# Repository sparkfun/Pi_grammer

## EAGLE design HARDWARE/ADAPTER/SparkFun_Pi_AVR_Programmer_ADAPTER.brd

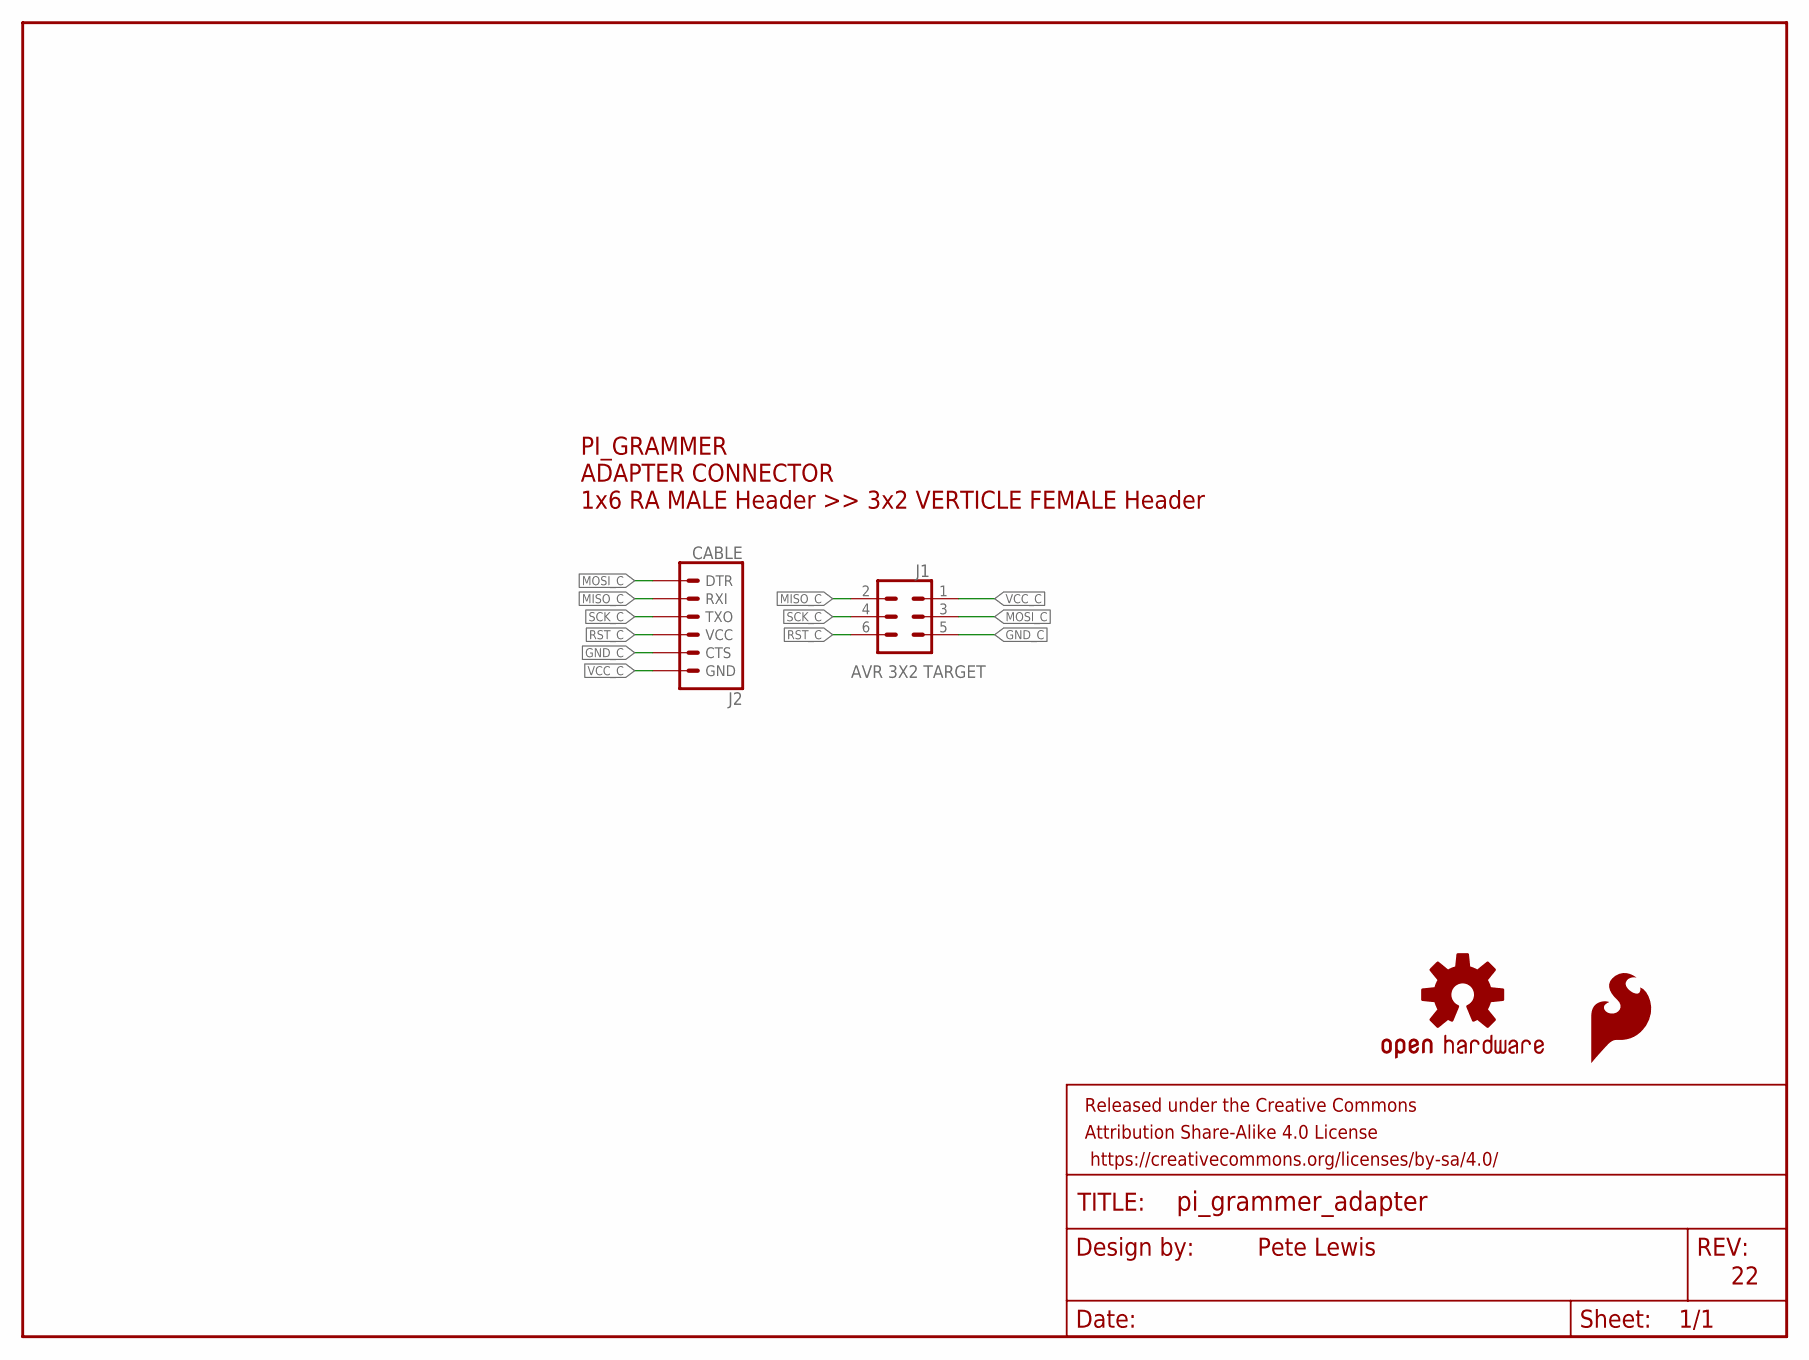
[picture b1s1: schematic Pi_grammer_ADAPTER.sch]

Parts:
FRAME1: FRAME-LETTER; CREATIVE_COMMONS
J1: AVR 3X2 TARGET; 2X3_SMT_POSTS
J2: CABLE; 1X06-SMD_RA_MALE
LOGO1: SFE_LOGO_FLAME.1_INCH; SFE_LOGO_FLAME_.1
LOGO2: OSHW-LOGOMINI; OSHW-LOGO-MINI

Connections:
GND_C: J1.5, J2.5 (CTS)
MISO_C: J1.2, J2.2 (RXI)
MOSI_C: J1.3, J2.1 (DTR)
RST_C: J1.6, J2.4 (VCC)
SCK_C: J1.4, J2.3 (TXO)
VCC_C: J1.1, J2.6 (GND)

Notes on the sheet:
PI_GRAMMER ADAPTER CONNECTOR 1x6 RA MALE Header >> 3x2 VERTICLE FEMALE Header
Pete Lewis

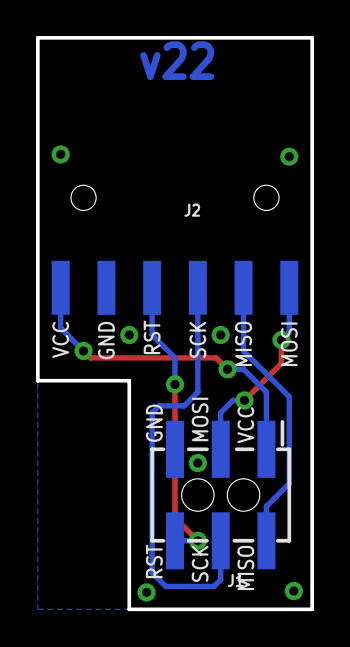
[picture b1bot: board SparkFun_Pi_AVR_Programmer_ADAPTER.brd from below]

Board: 2 copper layers, 15.2 x 31.8 mm, 16 parts (2 on the bottom side), 6 nets.

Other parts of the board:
U$1: GND1
U$2: MISO5
U$3: MOSI4
U$4: RST2
U$5: SCK3
U$6: VCC0
U$7: PI0
U$8: AVR1
U$9: PROGRAMMER2
U$10: HAT3
U$11: ADAPTER4

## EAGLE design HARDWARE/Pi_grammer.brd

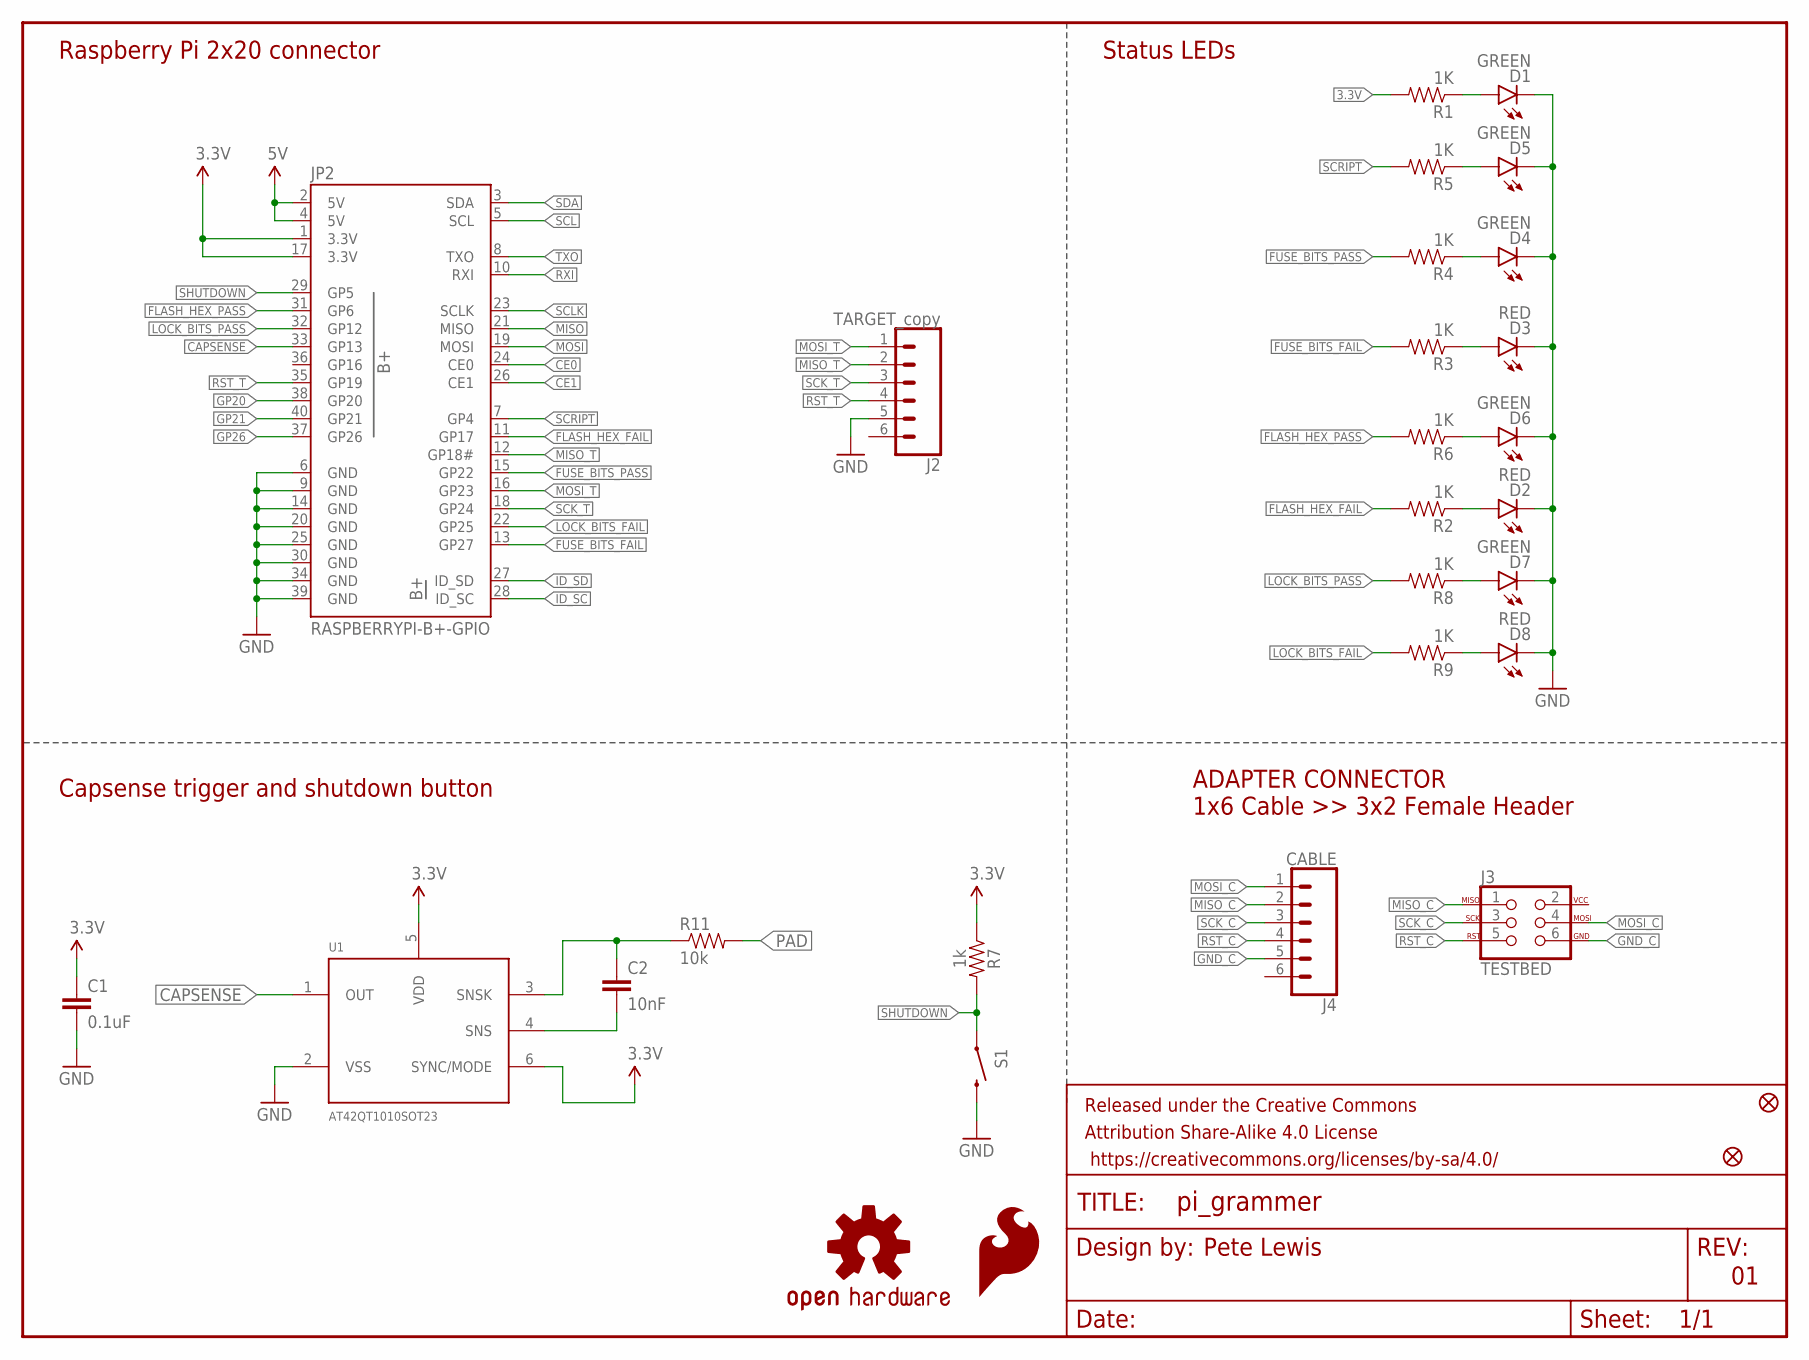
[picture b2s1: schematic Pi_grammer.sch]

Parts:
C1: 0.1uF; 0603-CAP
C2: 10nF; 0603-CAP
D1, D4, D5, D6, D7: GREEN; LED-1206
D2, D3, D8: RED; LED-1206
FD1, FD2: FIDUCIALUFIDUCIAL; FIDUCIAL-MICRO
FRAME1: FRAME-LETTER; CREATIVE_COMMONS
J2: TARGET_copy; MOLEX-1X6
J3: TESTBED; 2X3_LOCK
J4: CABLE; MOLEX-1X6-RA
JP2: RASPBERRYPI-B+-GPIO; 2X20-SHROUDED
LOGO1: SFE_LOGO_FLAME.1_INCH; SFE_LOGO_FLAME_.1
LOGO2: OSHW-LOGOS; OSHW-LOGO-S
R1, R2, R3, R4, R5, R6, R8, R9: 1K; 0603-RES
R7: 1k; 0603
R11: 10k; 0603-RES
S1: SWITCH-MOMENTARY-2SMD; TACTILE-SWITCH-SMD
U1: AT42QT1010SOT23; SOT23-6

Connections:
3.3V: C1.1, JP2.1 (3.3V), JP2.17 (3.3V), R1.2, R7.1, U1.5 (VDD), U1.6 (SYNC/MODE)
5V: JP2.2 (5V), JP2.4 (5V)
CAPSENSE: JP2.33 (GP13), U1.1 (OUT)
CE0: JP2.24 (CE0)
CE1: JP2.26 (CE1)
FLASH_HEX_FAIL: JP2.11 (GP17), R2.2
FLASH_HEX_PASS: JP2.31 (GP6), R6.2
FUSE_BITS_FAIL: JP2.13 (GP27), R3.2
FUSE_BITS_PASS: JP2.15 (GP22), R4.2
GND: C1.2, D1.C, D2.C, D3.C, D4.C, D5.C, D6.C, D7.C, D8.C, J2.5, JP2.6 (GND), JP2.9 (GND), JP2.14 (GND), JP2.20 (GND), JP2.25 (GND), JP2.30 (GND), JP2.34 (GND), JP2.39 (GND), S1.3 (2), U1.2 (VSS)
GND_C: J3.6, J4.5
GP20: JP2.38 (GP20)
GP21: JP2.40 (GP21)
GP26: JP2.37 (GP26)
ID_SC: JP2.28 (ID_SC)
ID_SD: JP2.27 (ID_SD)
LOCK_BITS_FAIL: JP2.22 (GP25), R9.2
LOCK_BITS_PASS: JP2.32 (GP12), R8.2
MISO: JP2.21 (MISO)
MISO_C: J3.1, J4.2
MISO_T: J2.2, JP2.12 (GP18#)
MOSI: JP2.19 (MOSI)
MOSI_C: J3.4, J4.1
MOSI_T: J2.1, JP2.16 (GP23)
unnamed: D6.A, R6.1
unnamed: D1.A, R1.1
unnamed: D2.A, R2.1
unnamed: D3.A, R3.1
unnamed: D7.A, R8.1
unnamed: D4.A, R4.1
unnamed: D5.A, R5.1
unnamed: D8.A, R9.1
unnamed: C2.2, U1.4 (SNS)
unnamed: C2.1, R11.1, U1.3 (SNSK)
PAD: R11.2
RST_C: J3.5, J4.4
RST_T: J2.4, JP2.35 (GP19)
RXI: JP2.10 (RXI)
SCK_C: J3.3, J4.3
SCK_T: J2.3, JP2.18 (GP24)
SCL: JP2.5 (SCL)
SCLK: JP2.23 (SCLK)
SCRIPT: JP2.7 (GP4), R5.2
SDA: JP2.3 (SDA)
SHUTDOWN: JP2.29 (GP5), R7.2, S1.1
TXO: JP2.8 (TXO)

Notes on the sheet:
ADAPTER CONNECTOR 1x6 Cable >> 3x2 Female Header
Raspberry Pi 2x20 connector
Pete Lewis
Status LEDs
Capsense trigger and shutdown button

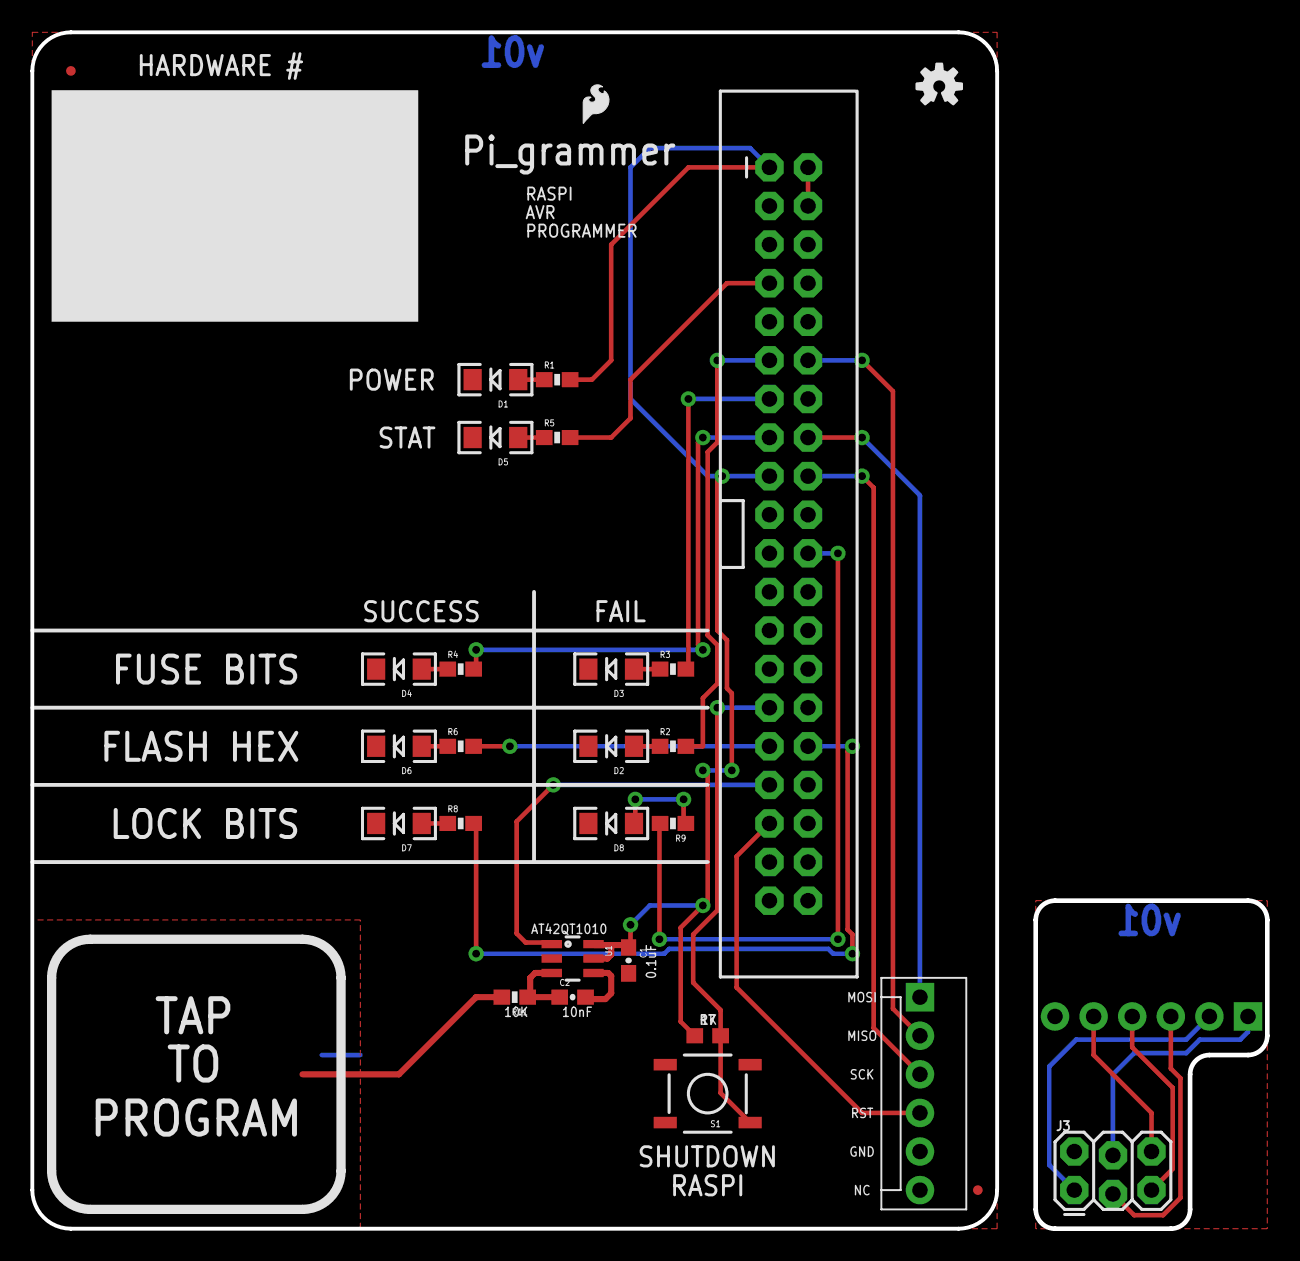
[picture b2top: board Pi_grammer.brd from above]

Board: 2 copper layers, 63.5 x 78.7 mm, 31 parts (1 on the bottom side), 31 nets.

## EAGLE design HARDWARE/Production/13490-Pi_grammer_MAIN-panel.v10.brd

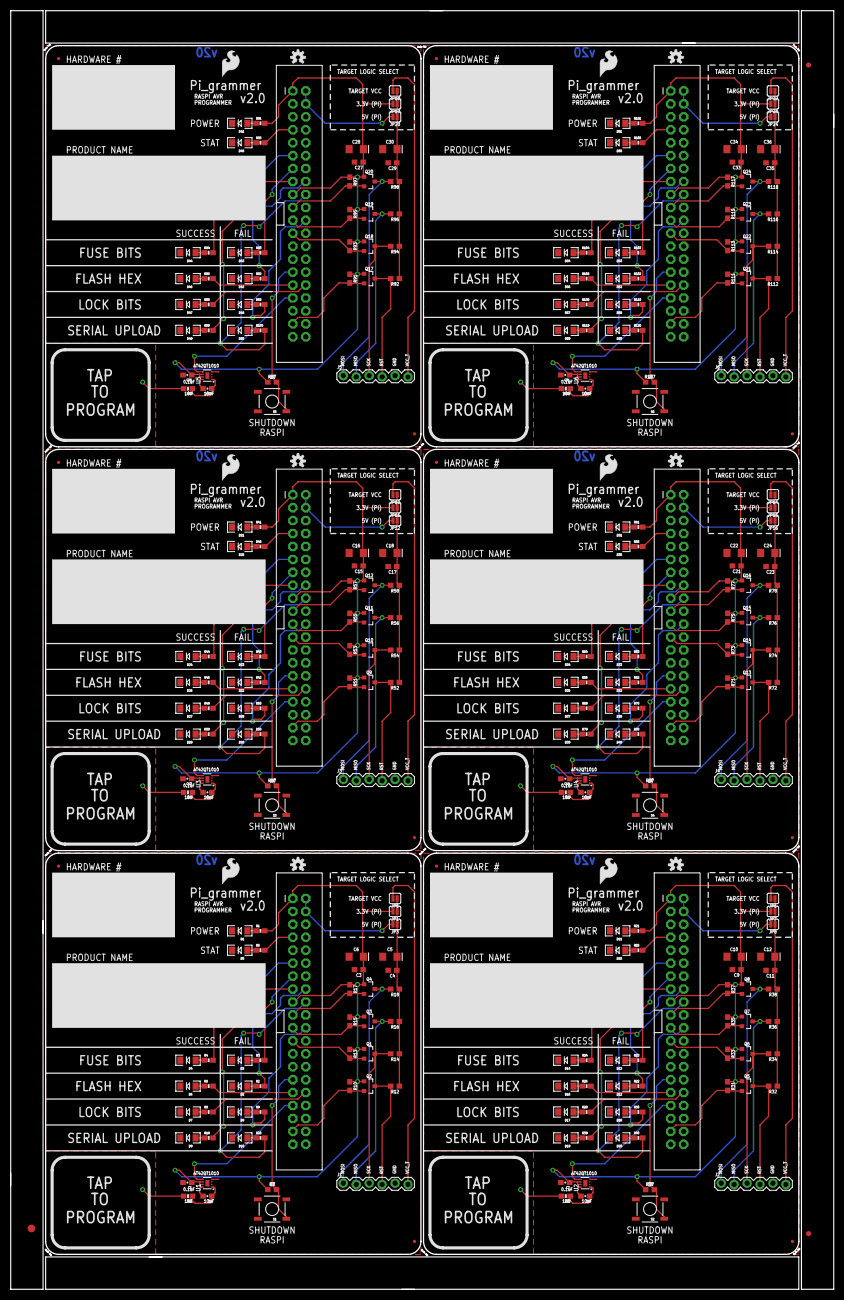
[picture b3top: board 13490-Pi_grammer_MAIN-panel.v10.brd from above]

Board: 2 copper layers, 161.5 x 251.0 mm, 309 parts (0 on the bottom side), 216 nets.

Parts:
C1, C7, C13, C19, C25, C31: 0.1uF; 0603-CAP
C2, C8, C14, C20, C26, C32: 10nF; 0603-CAP
C3, C4, C9, C11, C15, C17, C21, C23, C27, C29, C33, C35: 0.1uF; 0603
C5, C6, C10, C12, C16, C18, C22, C24, C28, C30, C34, C36: 10uF; EIA3216
D1, D4, D5, D6, D7, D9, D11, D14, D15, D16, D17, D19, D21, D24, D25, D26, D27, D29, D31, D34, D35, D36, D37, D39, D41, D44, D45, D46, D47, D49, D51, D54, D55, D56, D57, D59: GREEN; LED-1206
D2, D3, D8, D10, D12, D13, D18, D20, D22, D23, D28, D30, D32, D33, D38, D40, D42, D43, D48, D50, D52, D53, D58, D60: RED; LED-1206
E$1: FIDUCIAL-1.5X3
E$7, E$8: FIDUCIAL-1X2
FD1, FD2, FD3, FD4, FD5, FD6, FD7, FD8, FD9, FD10, FD11, FD12: FIDUCIALUFIDUCIAL; MICRO-FIDUCIAL
J1, J2, J3, J4, J5, J6: TARGET_copy; 1X06_LOCK
JP1, JP3, JP5, JP6, JP7, JP8, JP10, JP11, JP12, JP14, JP15, JP16, JP18, JP19, JP20, JP22, JP23, JP24: SMT-JUMPER_2_NO_SILK
JP2, JP4, JP9, JP13, JP17, JP21: RASPBERRYPI-B+-GPIO; 2X20-SHROUDED
LOGO1, LOGO4, LOGO6, LOGO8, LOGO10, LOGO12: SFE_LOGO_FLAME.2_INCH; SFE_LOGO_FLAME_.2
LOGO2, LOGO3, LOGO5, LOGO7, LOGO9, LOGO11: OSHW-LOGOS; OSHW-LOGO-S
Q1, Q2, Q3, Q4, Q5, Q6, Q7, Q8, Q9, Q10, Q11, Q12, Q13, Q14, Q15, Q16, Q17, Q18, Q19, Q20, Q21, Q22, Q23, Q24: 220mA/50V/3.5Ω; SOT23-3
R1, R2, R3, R4, R5, R6, R8, R9, R19, R20, R21, R22, R23, R24, R25, R26, R28, R30, R39, R40, R41, R42, R43, R44, R45, R46, R48, R50, R59, R60, R61, R62, R63, R64, R65, R66, R68, R70, R79, R80, R81, R82, R83, R84, R85, R86, R88, R90, R99, R100, R101, R102, R103, R104, R105, R106, R108, R110, R119, R120: 1K; 0603-RES
R7, R27, R47, R67, R87, R107: 1k; 0603
R10, R12, R13, R14, R15, R16, R17, R18, R31, R32, R33, R34, R35, R36, R37, R38, R51, R52, R53, R54, R55, R56, R57, R58, R71, R72, R73, R74, R75, R76, R77, R78, R91, R92, R93, R94, R95, R96, R97, R98, R111, R112, R113, R114, R115, R116, R117, R118: 10k; 0603
R11, R29, R49, R69, R89, R109: 10k; 0603-RES
S1, S2, S3, S4, S5, S6: TACTILE-SWITCH-SMD
U1, U2, U3, U4, U5, U6: AT42QT1010UDFN; UDFN/USON_8_PAD

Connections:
3.3V: C1.1, C3.1, C6.+, JP1.2, JP2.1, JP2.17, Q1.1, Q2.1, Q3.1, Q4.1, R1.2, R7.1, R10.1, R13.1, R15.1, R17.1, U1.6, U1.7
3.3V1: C7.1, C9.1, C10.+, JP4.1, JP4.17, JP7.2, Q5.1, Q6.1, Q7.1, Q8.1, R21.2, R27.1, R31.1, R33.1, R35.1, R37.1, U2.6, U2.7
3.3V2: C13.1, C15.1, C16.+, JP9.1, JP9.17, JP11.2, Q9.1, Q10.1, Q11.1, Q12.1, R41.2, R47.1, R51.1, R53.1, R55.1, R57.1, U3.6, U3.7
3.3V3: C19.1, C21.1, C22.+, JP13.1, JP13.17, JP15.2, Q13.1, Q14.1, Q15.1, Q16.1, R61.2, R67.1, R71.1, R73.1, R75.1, R77.1, U4.6, U4.7
3.3V4: C25.1, C27.1, C28.+, JP17.1, JP17.17, JP19.2, Q17.1, Q18.1, Q19.1, Q20.1, R81.2, R87.1, R91.1, R93.1, R95.1, R97.1, U5.6, U5.7
3.3V5: C31.1, C33.1, C34.+, JP21.1, JP21.17, JP23.2, Q21.1, Q22.1, Q23.1, Q24.1, R101.2, R107.1, R111.1, R113.1, R115.1, R117.1, U6.6, U6.7
5V: JP2.2, JP2.4, JP3.2
5V1: JP4.2, JP4.4, JP8.2
5V2: JP9.2, JP9.4, JP12.2
5V3: JP13.2, JP13.4, JP16.2
5V4: JP17.2, JP17.4, JP20.2
5V5: JP21.2, JP21.4, JP24.2
CAPSENSE: JP2.33, U1.5
CAPSENSE1: JP4.33, U2.5
CAPSENSE2: JP9.33, U3.5
CAPSENSE3: JP13.33, U4.5
CAPSENSE4: JP17.33, U5.5
CAPSENSE5: JP21.33, U6.5
FLASH_HEX_FAIL: JP2.11, R2.2
FLASH_HEX_FAIL1: JP4.11, R22.2
FLASH_HEX_FAIL2: JP9.11, R42.2
FLASH_HEX_FAIL3: JP13.11, R62.2
FLASH_HEX_FAIL4: JP17.11, R82.2
FLASH_HEX_FAIL5: JP21.11, R102.2
FLASH_HEX_PASS: JP2.31, R6.2
FLASH_HEX_PASS1: JP4.31, R26.2
FLASH_HEX_PASS2: JP9.31, R46.2
FLASH_HEX_PASS3: JP13.31, R66.2
FLASH_HEX_PASS4: JP17.31, R86.2
FLASH_HEX_PASS5: JP21.31, R106.2
FUSE_BITS_FAIL: JP2.13, R3.2
FUSE_BITS_FAIL1: JP4.13, R23.2
FUSE_BITS_FAIL2: JP9.13, R43.2
FUSE_BITS_FAIL3: JP13.13, R63.2
FUSE_BITS_FAIL4: JP17.13, R83.2
FUSE_BITS_FAIL5: JP21.13, R103.2
FUSE_BITS_PASS: JP2.15, R4.2
FUSE_BITS_PASS1: JP4.15, R24.2
FUSE_BITS_PASS2: JP9.15, R44.2
FUSE_BITS_PASS3: JP13.15, R64.2
FUSE_BITS_PASS4: JP17.15, R84.2
FUSE_BITS_PASS5: JP21.15, R104.2
GND: C1.2, C3.2, C4.2, C5.-, C6.-, D1.C, D2.C, D3.C, D4.C, D5.C, D6.C, D7.C, D8.C, D9.C, D10.C, J1.5, JP2.6, JP2.9, JP2.14, JP2.20, JP2.25, JP2.30, JP2.34, JP2.39, S1.3, U1.4
GND1: C7.2, C9.2, C10.-, C11.2, C12.-, D11.C, D12.C, D13.C, D14.C, D15.C, D16.C, D17.C, D18.C, D19.C, D20.C, J2.5, JP4.6, JP4.9, JP4.14, JP4.20, JP4.25, JP4.30, JP4.34, JP4.39, S2.3, U2.4
GND2: C13.2, C15.2, C16.-, C17.2, C18.-, D21.C, D22.C, D23.C, D24.C, D25.C, D26.C, D27.C, D28.C, D29.C, D30.C, J3.5, JP9.6, JP9.9, JP9.14, JP9.20, JP9.25, JP9.30, JP9.34, JP9.39, S3.3, U3.4
GND3: C19.2, C21.2, C22.-, C23.2, C24.-, D31.C, D32.C, D33.C, D34.C, D35.C, D36.C, D37.C, D38.C, D39.C, D40.C, J4.5, JP13.6, JP13.9, JP13.14, JP13.20, JP13.25, JP13.30, JP13.34, JP13.39, S4.3, U4.4
GND4: C25.2, C27.2, C28.-, C29.2, C30.-, D41.C, D42.C, D43.C, D44.C, D45.C, D46.C, D47.C, D48.C, D49.C, D50.C, J5.5, JP17.6, JP17.9, JP17.14, JP17.20, JP17.25, JP17.30, JP17.34, JP17.39, S5.3, U5.4
GND5: C31.2, C33.2, C34.-, C35.2, C36.-, D51.C, D52.C, D53.C, D54.C, D55.C, D56.C, D57.C, D58.C, D59.C, D60.C, J6.5, JP21.6, JP21.9, JP21.14, JP21.20, JP21.25, JP21.30, JP21.34, JP21.39, S6.3, U6.4
LOCK_BITS_FAIL: JP2.22, R9.2
LOCK_BITS_FAIL1: JP4.22, R30.2
LOCK_BITS_FAIL2: JP9.22, R50.2
LOCK_BITS_FAIL3: JP13.22, R70.2
LOCK_BITS_FAIL4: JP17.22, R90.2
LOCK_BITS_FAIL5: JP21.22, R110.2
LOCK_BITS_PASS: JP2.32, R8.2
LOCK_BITS_PASS1: JP4.32, R28.2
LOCK_BITS_PASS2: JP9.32, R48.2
LOCK_BITS_PASS3: JP13.32, R68.2
LOCK_BITS_PASS4: JP17.32, R88.2
LOCK_BITS_PASS5: JP21.32, R108.2
MISO: JP2.21, Q3.2, R15.2
MISO1: JP4.21, Q7.2, R35.2
MISO2: JP9.21, Q11.2, R55.2
MISO3: JP13.21, Q15.2, R75.2
MISO4: JP17.21, Q19.2, R95.2
MISO5: JP21.21, Q23.2, R115.2
MISO_T: J1.2, Q3.3, R16.2
MISO_T1: J2.2, Q7.3, R36.2
MISO_T2: J3.2, Q11.3, R56.2
MISO_T3: J4.2, Q15.3, R76.2
MISO_T4: J5.2, Q19.3, R96.2
MISO_T5: J6.2, Q23.3, R116.2
MOSI: JP2.19, Q4.2, R17.2
MOSI1: JP4.19, Q8.2, R37.2
MOSI2: JP9.19, Q12.2, R57.2
MOSI3: JP13.19, Q16.2, R77.2
MOSI4: JP17.19, Q20.2, R97.2
MOSI5: JP21.19, Q24.2, R117.2
MOSI_T: J1.1, Q4.3, R18.2
MOSI_T1: J2.1, Q8.3, R38.2
MOSI_T2: J3.1, Q12.3, R58.2
MOSI_T3: J4.1, Q16.3, R78.2
MOSI_T4: J5.1, Q20.3, R98.2
MOSI_T5: J6.1, Q24.3, R118.2
unnamed: D6.A, R6.1
unnamed: D1.A, R1.1
unnamed: D2.A, R2.1
unnamed: D3.A, R3.1
unnamed: D7.A, R8.1
unnamed: D4.A, R4.1
unnamed: D5.A, R5.1
unnamed: D8.A, R9.1
unnamed: C4.1, C5.+, JP1.1, JP3.1, JP5.1, R12.1, R14.1, R16.1, R18.1
unnamed: C2.2, U1.8
unnamed: C2.1, R11.1, U1.1
unnamed: D11.A, R21.1
unnamed: D9.A, R19.1
unnamed: D10.A, R20.1
unnamed: D12.A, R22.1
unnamed: D13.A, R23.1
unnamed: D14.A, R24.1
unnamed: D15.A, R25.1
unnamed: D16.A, R26.1
unnamed: D17.A, R28.1
unnamed: C8.2, U2.8
unnamed: C8.1, R29.1, U2.1
unnamed: D18.A, R30.1
unnamed: D19.A, R39.1
unnamed: D20.A, R40.1
unnamed: C11.1, C12.+, JP6.1, JP7.1, JP8.1, R32.1, R34.1, R36.1, R38.1
unnamed: D21.A, R41.1
unnamed: D22.A, R42.1
unnamed: D23.A, R43.1
unnamed: D24.A, R44.1
unnamed: D25.A, R45.1
unnamed: D26.A, R46.1
unnamed: D27.A, R48.1
unnamed: C14.2, U3.8
unnamed: C14.1, R49.1, U3.1
unnamed: D28.A, R50.1
unnamed: D29.A, R59.1
unnamed: D30.A, R60.1
unnamed: C17.1, C18.+, JP10.1, JP11.1, JP12.1, R52.1, R54.1, R56.1, R58.1
unnamed: D31.A, R61.1
unnamed: D32.A, R62.1
unnamed: D33.A, R63.1
unnamed: D34.A, R64.1
unnamed: D35.A, R65.1
unnamed: D36.A, R66.1
unnamed: D37.A, R68.1
unnamed: C20.2, U4.8
unnamed: C20.1, R69.1, U4.1
unnamed: D38.A, R70.1
unnamed: D39.A, R79.1
unnamed: D40.A, R80.1
unnamed: C23.1, C24.+, JP14.1, JP15.1, JP16.1, R72.1, R74.1, R76.1, R78.1
unnamed: D41.A, R81.1
unnamed: D42.A, R82.1
unnamed: D43.A, R83.1
unnamed: D44.A, R84.1
unnamed: D45.A, R85.1
unnamed: D46.A, R86.1
unnamed: D47.A, R88.1
unnamed: C26.2, U5.8
unnamed: C26.1, R89.1, U5.1
unnamed: D48.A, R90.1
unnamed: D49.A, R99.1
unnamed: D50.A, R100.1
unnamed: C29.1, C30.+, JP18.1, JP19.1, JP20.1, R92.1, R94.1, R96.1, R98.1
unnamed: D51.A, R101.1
unnamed: D52.A, R102.1
unnamed: D53.A, R103.1
unnamed: D54.A, R104.1
unnamed: D55.A, R105.1
unnamed: D56.A, R106.1
unnamed: D57.A, R108.1
unnamed: C32.2, U6.8
unnamed: C32.1, R109.1, U6.1
unnamed: D58.A, R110.1
unnamed: D59.A, R119.1
unnamed: D60.A, R120.1
unnamed: C35.1, C36.+, JP22.1, JP23.1, JP24.1, R112.1, R114.1, R116.1, R118.1
RST: JP2.37, Q2.2, R10.2
RST1: JP4.37, Q5.2, R31.2
RST2: JP9.37, Q9.2, R51.2
RST3: JP13.37, Q13.2, R71.2
RST4: JP17.37, Q17.2, R91.2
RST5: JP21.37, Q21.2, R111.2
RST_T: J1.4, Q2.3, R12.2
RST_T1: J2.4, Q5.3, R32.2
RST_T2: J3.4, Q9.3, R52.2
RST_T3: J4.4, Q13.3, R72.2
RST_T4: J5.4, Q17.3, R92.2
RST_T5: J6.4, Q21.3, R112.2
SCK: JP2.23, Q1.2, R13.2
SCK1: JP4.23, Q6.2, R33.2
SCK2: JP9.23, Q10.2, R53.2
SCK3: JP13.23, Q14.2, R73.2
SCK4: JP17.23, Q18.2, R93.2
SCK5: JP21.23, Q22.2, R113.2
SCK_T: J1.3, Q1.3, R14.2
SCK_T1: J2.3, Q6.3, R34.2
SCK_T2: J3.3, Q10.3, R54.2
SCK_T3: J4.3, Q14.3, R74.2
SCK_T4: J5.3, Q18.3, R94.2
SCK_T5: J6.3, Q22.3, R114.2
SCRIPT: JP2.7, R5.2
SCRIPT1: JP4.7, R25.2
SCRIPT2: JP9.7, R45.2
SCRIPT3: JP13.7, R65.2
SCRIPT4: JP17.7, R85.2
SCRIPT5: JP21.7, R105.2
SERIAL_UPLOAD_FAIL: JP2.18, R20.2
SERIAL_UPLOAD_FAIL1: JP4.18, R40.2
SERIAL_UPLOAD_FAIL2: JP9.18, R60.2
SERIAL_UPLOAD_FAIL3: JP13.18, R80.2
SERIAL_UPLOAD_FAIL4: JP17.18, R100.2
SERIAL_UPLOAD_FAIL5: JP21.18, R120.2
SERIAL_UPLOAD_PASS: JP2.16, R19.2
SERIAL_UPLOAD_PASS1: JP4.16, R39.2
SERIAL_UPLOAD_PASS2: JP9.16, R59.2
SERIAL_UPLOAD_PASS3: JP13.16, R79.2
SERIAL_UPLOAD_PASS4: JP17.16, R99.2
SERIAL_UPLOAD_PASS5: JP21.16, R119.2
SHUTDOWN: JP2.29, R7.2, S1.1
SHUTDOWN1: JP4.29, R27.2, S2.1
SHUTDOWN2: JP9.29, R47.2, S3.1
SHUTDOWN3: JP13.29, R67.2, S4.1
SHUTDOWN4: JP17.29, R87.2, S5.1
SHUTDOWN5: JP21.29, R107.2, S6.1
VCC_T: J1.6, JP5.2
VCC_T1: J2.6, JP6.2
VCC_T2: J3.6, JP10.2
VCC_T3: J4.6, JP14.2
VCC_T4: J5.6, JP18.2
VCC_T5: J6.6, JP22.2

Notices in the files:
parts and their libraries:
SparkFun-Aesthetics: Licensing: CC v3.0 Share-Alike You are welcome to use this library for commercial purposes.
SparkFun-Aesthetics: Released under the Creative Commons Attribution Share-Alike 4.0 License
SparkFun-Aesthetics: https://creativecommons.org/licenses/by-sa/4.0
